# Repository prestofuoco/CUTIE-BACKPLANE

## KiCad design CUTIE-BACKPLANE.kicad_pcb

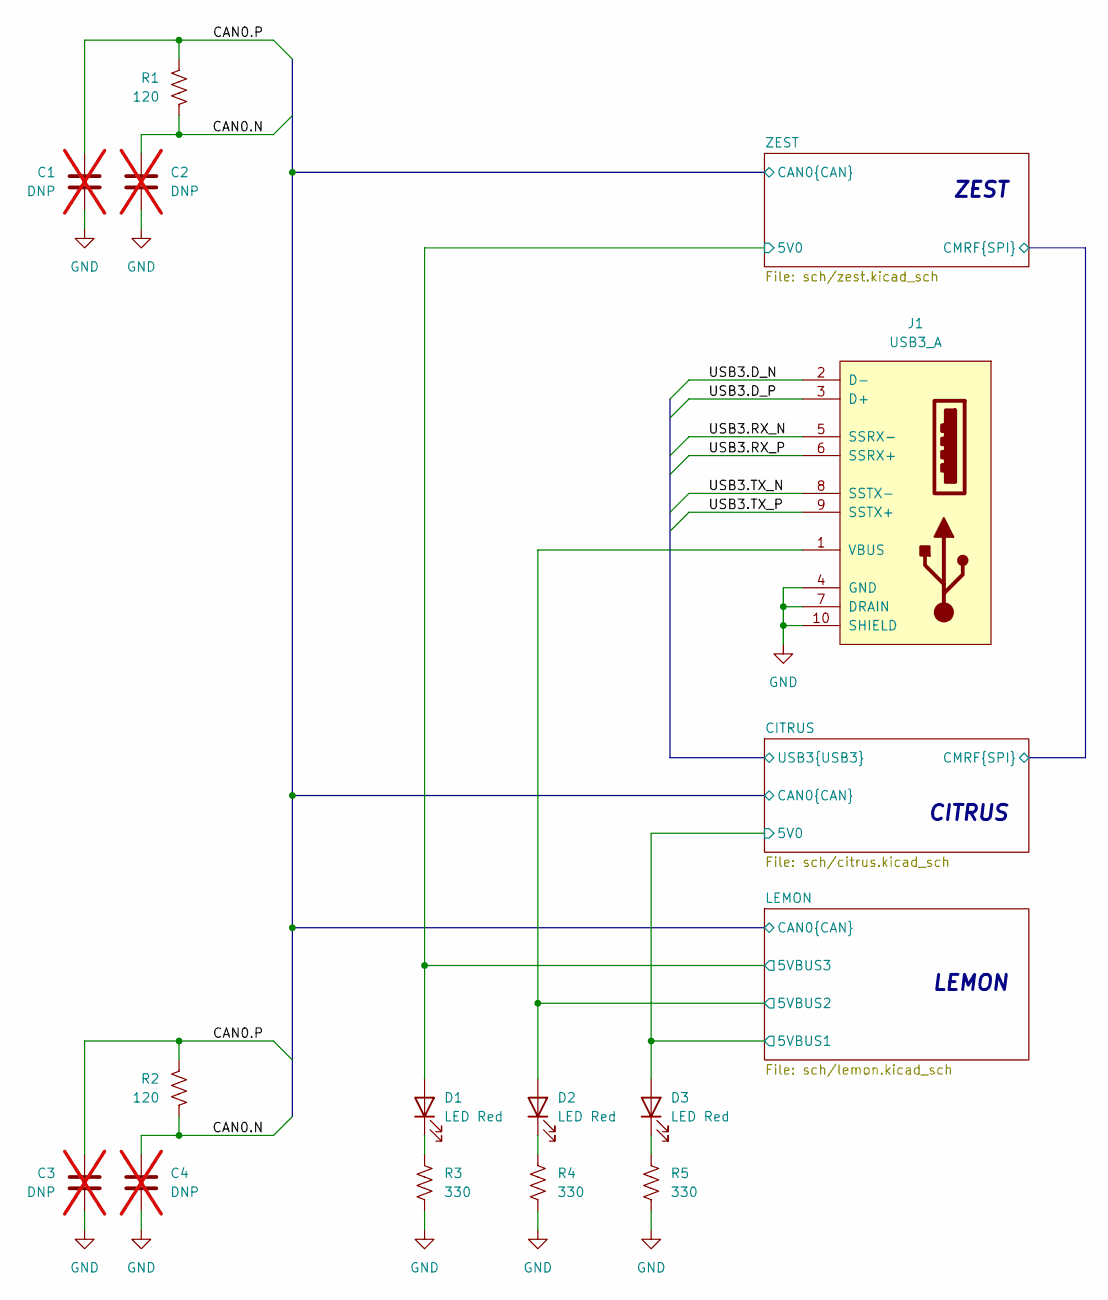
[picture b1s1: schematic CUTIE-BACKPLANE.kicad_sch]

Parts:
C1, C2, C3, C4: DNP; C_0402_1005Metric; not fitted
D1, D2, D3: LED Red; LED_0805_2012Metric
J1: USB3_A; CONN9_08-0003_MOL
R1, R2: 120; R_0402_1005Metric
R3, R4, R5: 330; R_0402_1005Metric

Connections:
/CITRUS/5V0: D3.2 (A); also elsewhere on the board
/CITRUS/CAN0.N: C2.2, C4.2, R1.2, R2.2; also elsewhere on the board
/CITRUS/CAN0.P: C1.2, C3.2, R1.1, R2.1; also elsewhere on the board
/CITRUS/USB3.D_N: J1.2 (D-); also elsewhere on the board
/CITRUS/USB3.D_P: J1.3 (D+); also elsewhere on the board
/CITRUS/USB3.RX_N: J1.5 (SSRX-); also elsewhere on the board
/CITRUS/USB3.RX_P: J1.6 (SSRX+); also elsewhere on the board
/CITRUS/USB3.TX_N: J1.8 (SSTX-); also elsewhere on the board
/CITRUS/USB3.TX_P: J1.9 (SSTX+); also elsewhere on the board
/LEMON/5VBUS2: D2.2 (A), J1.1 (VBUS); also elsewhere on the board
/LEMON/5VBUS3: D1.2 (A); also elsewhere on the board
GND: C1.1, C2.1, C3.1, C4.1, J1.4 (GND), J1.7 (DRAIN), J1.10 (SHIELD), R3.2, R4.2, R5.2; also elsewhere on the board
unnamed: D1.1 (K), R3.1
unnamed: D2.1 (K), R4.1
unnamed: D3.1 (K), R5.1

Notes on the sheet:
CITRUS
ZEST
LEMON

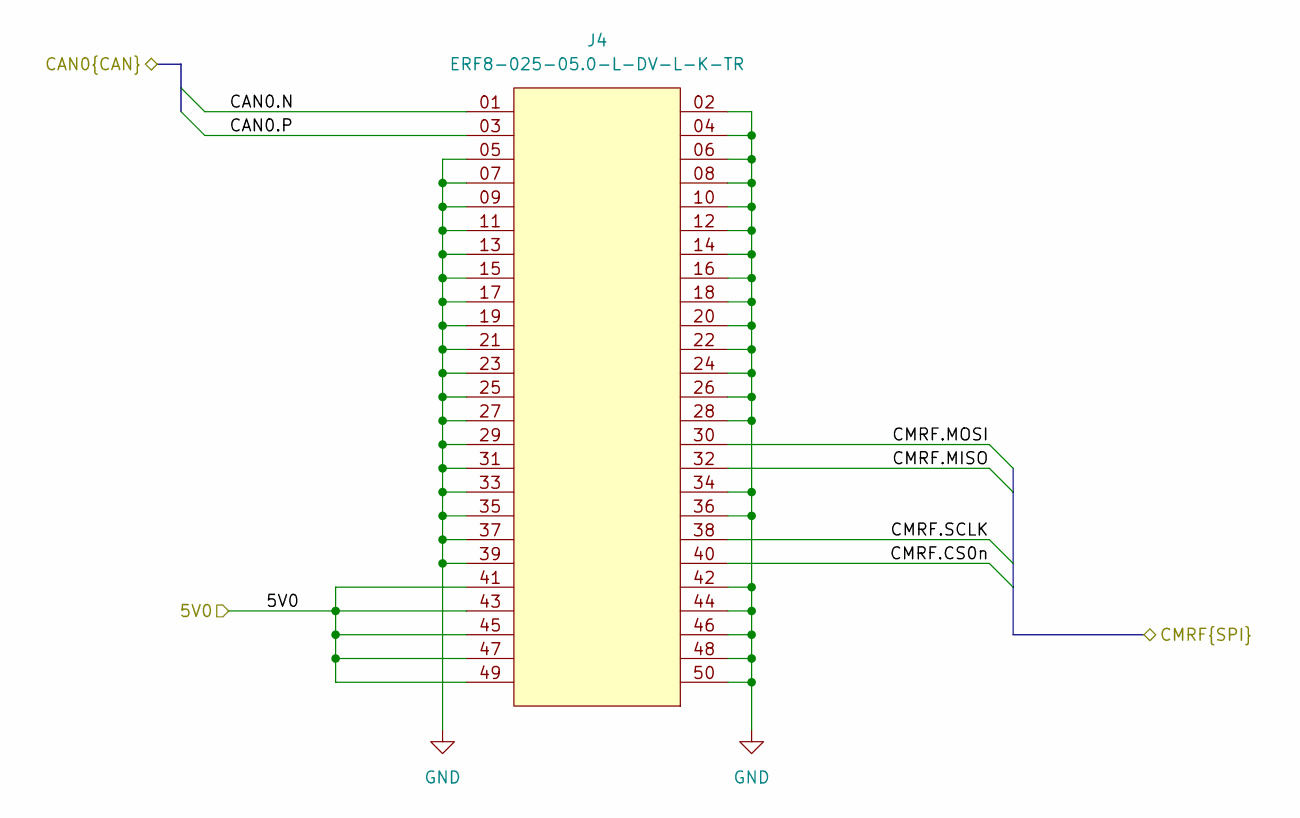
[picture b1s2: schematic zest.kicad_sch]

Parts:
J4: ERF8-025-05.0-L-DV-L-K-TR; SAMTEC_ERF8-025-05.0-L-DV-L-K-TR

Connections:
/CITRUS/CAN0.N: J4.01; also elsewhere on the board
/CITRUS/CAN0.P: J4.03; also elsewhere on the board
/CITRUS/CMRF.CS0n: J4.40; also elsewhere on the board
/CITRUS/CMRF.MISO: J4.32; also elsewhere on the board
/CITRUS/CMRF.MOSI: J4.30; also elsewhere on the board
/CITRUS/CMRF.SCLK: J4.38; also elsewhere on the board
/LEMON/5VBUS3: J4.41, J4.43, J4.45, J4.47, J4.49; also elsewhere on the board
GND: J4.02, J4.04, J4.05, J4.06, J4.07, J4.08, J4.09, J4.10, J4.11, J4.12, J4.13, J4.14, J4.15, J4.16, J4.17, J4.18, J4.19, J4.20, J4.21, J4.22, J4.23, J4.24, J4.25, J4.26, J4.27, J4.28, J4.29, J4.31, J4.33, J4.34, J4.35, J4.36, J4.37, J4.39, J4.42, J4.44, J4.46, J4.48, J4.50; also elsewhere on the board

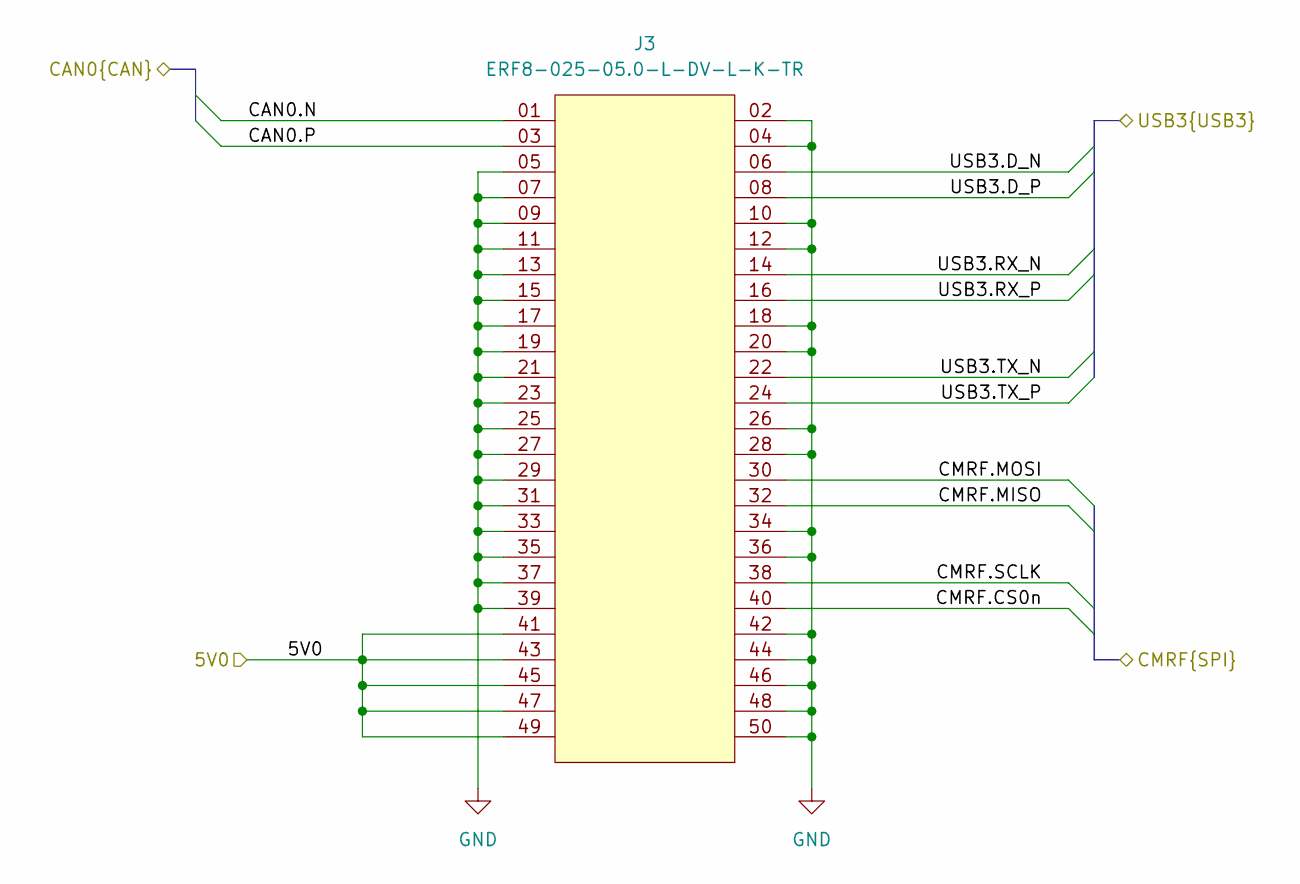
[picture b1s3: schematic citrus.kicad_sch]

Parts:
J3: ERF8-025-05.0-L-DV-L-K-TR; SAMTEC_ERF8-025-05.0-L-DV-L-K-TR

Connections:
/CITRUS/5V0: J3.41, J3.43, J3.45, J3.47, J3.49; also elsewhere on the board
/CITRUS/CAN0.N: J3.01; also elsewhere on the board
/CITRUS/CAN0.P: J3.03; also elsewhere on the board
/CITRUS/CMRF.CS0n: J3.40; also elsewhere on the board
/CITRUS/CMRF.MISO: J3.32; also elsewhere on the board
/CITRUS/CMRF.MOSI: J3.30; also elsewhere on the board
/CITRUS/CMRF.SCLK: J3.38; also elsewhere on the board
/CITRUS/USB3.D_N: J3.06; also elsewhere on the board
/CITRUS/USB3.D_P: J3.08; also elsewhere on the board
/CITRUS/USB3.RX_N: J3.14; also elsewhere on the board
/CITRUS/USB3.RX_P: J3.16; also elsewhere on the board
/CITRUS/USB3.TX_N: J3.22; also elsewhere on the board
/CITRUS/USB3.TX_P: J3.24; also elsewhere on the board
GND: J3.02, J3.04, J3.05, J3.07, J3.09, J3.10, J3.11, J3.12, J3.13, J3.15, J3.17, J3.18, J3.19, J3.20, J3.21, J3.23, J3.25, J3.26, J3.27, J3.28, J3.29, J3.31, J3.33, J3.34, J3.35, J3.36, J3.37, J3.39, J3.42, J3.44, J3.46, J3.48, J3.50; also elsewhere on the board

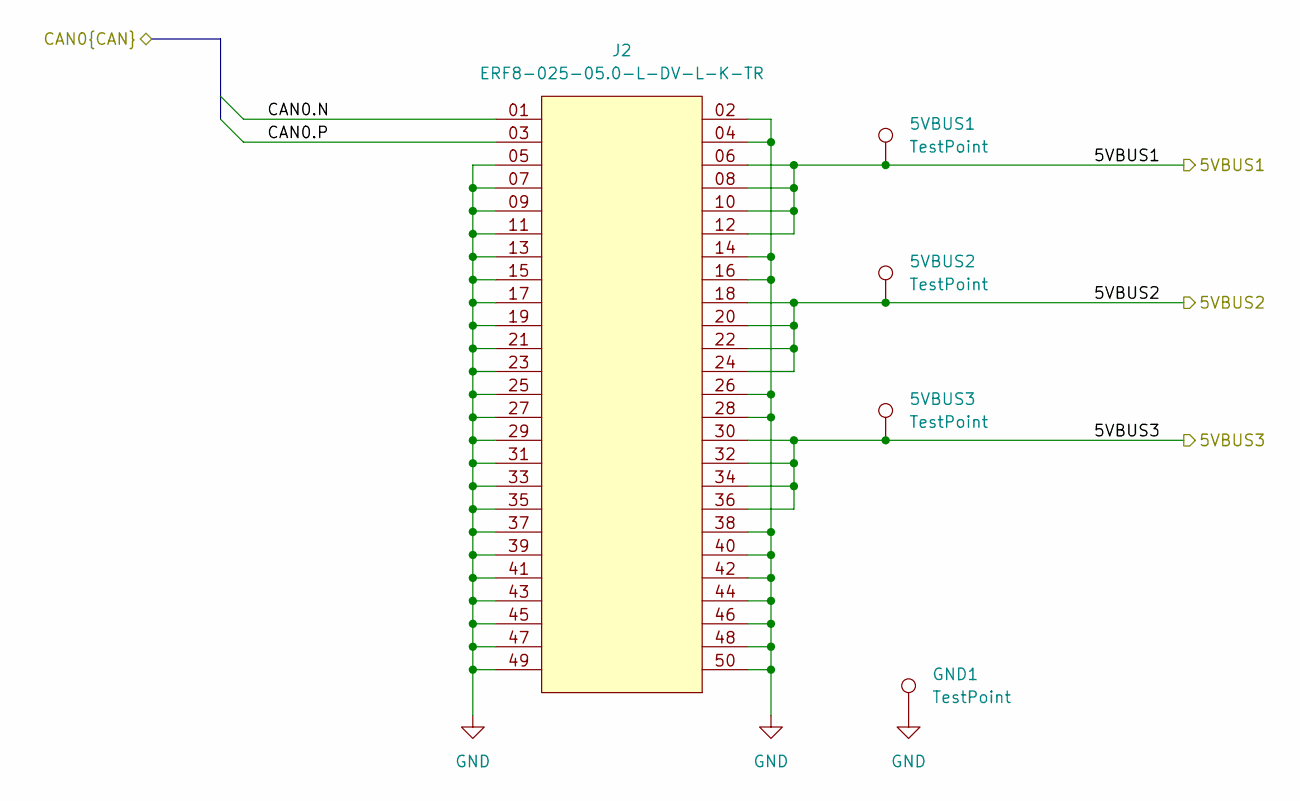
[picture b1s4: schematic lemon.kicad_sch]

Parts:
5VBUS1, 5VBUS2, 5VBUS3: TestPoint; KEYSTONE_575-4
GND1: TestPoint; KEYSTONE_575-4
J2: ERF8-025-05.0-L-DV-L-K-TR; SAMTEC_ERF8-025-05.0-L-DV-L-K-TR

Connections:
/CITRUS/5V0: 5VBUS1.1 (1_1), J2.06, J2.08, J2.10, J2.12; also elsewhere on the board
/CITRUS/CAN0.N: J2.01; also elsewhere on the board
/CITRUS/CAN0.P: J2.03; also elsewhere on the board
/LEMON/5VBUS2: 5VBUS2.1 (1_1), J2.18, J2.20, J2.22, J2.24; also elsewhere on the board
/LEMON/5VBUS3: 5VBUS3.1 (1_1), J2.30, J2.32, J2.34, J2.36; also elsewhere on the board
GND: GND1.1, J2.02, J2.04, J2.05, J2.07, J2.09, J2.11, J2.13, J2.14, J2.15, J2.16, J2.17, J2.19, J2.21, J2.23, J2.25, J2.26, J2.27, J2.28, J2.29, J2.31, J2.33, J2.35, J2.37, J2.38, J2.39, J2.40, J2.41, J2.42, J2.43, J2.44, J2.45, J2.46, J2.47, J2.48, J2.49, J2.50; also elsewhere on the board

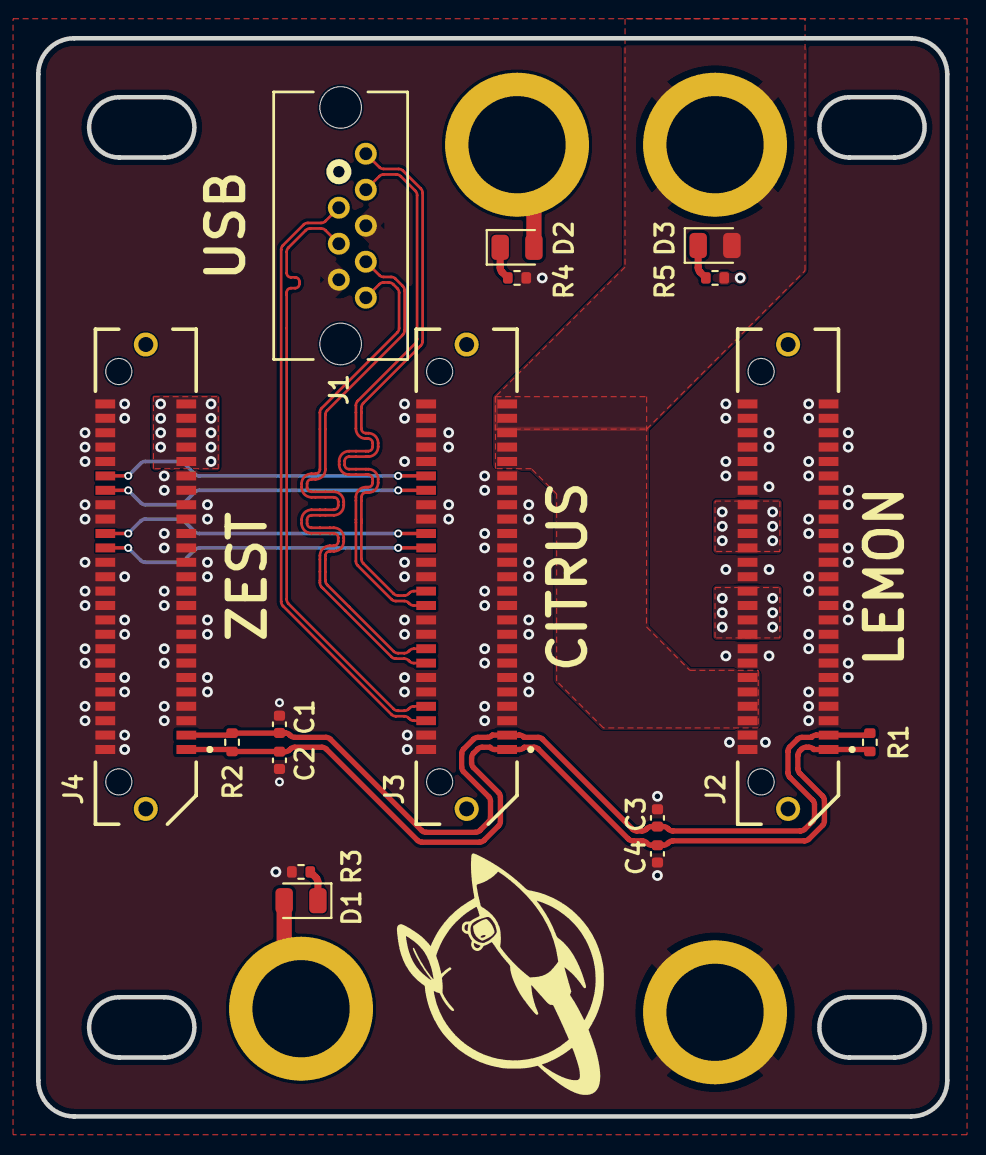
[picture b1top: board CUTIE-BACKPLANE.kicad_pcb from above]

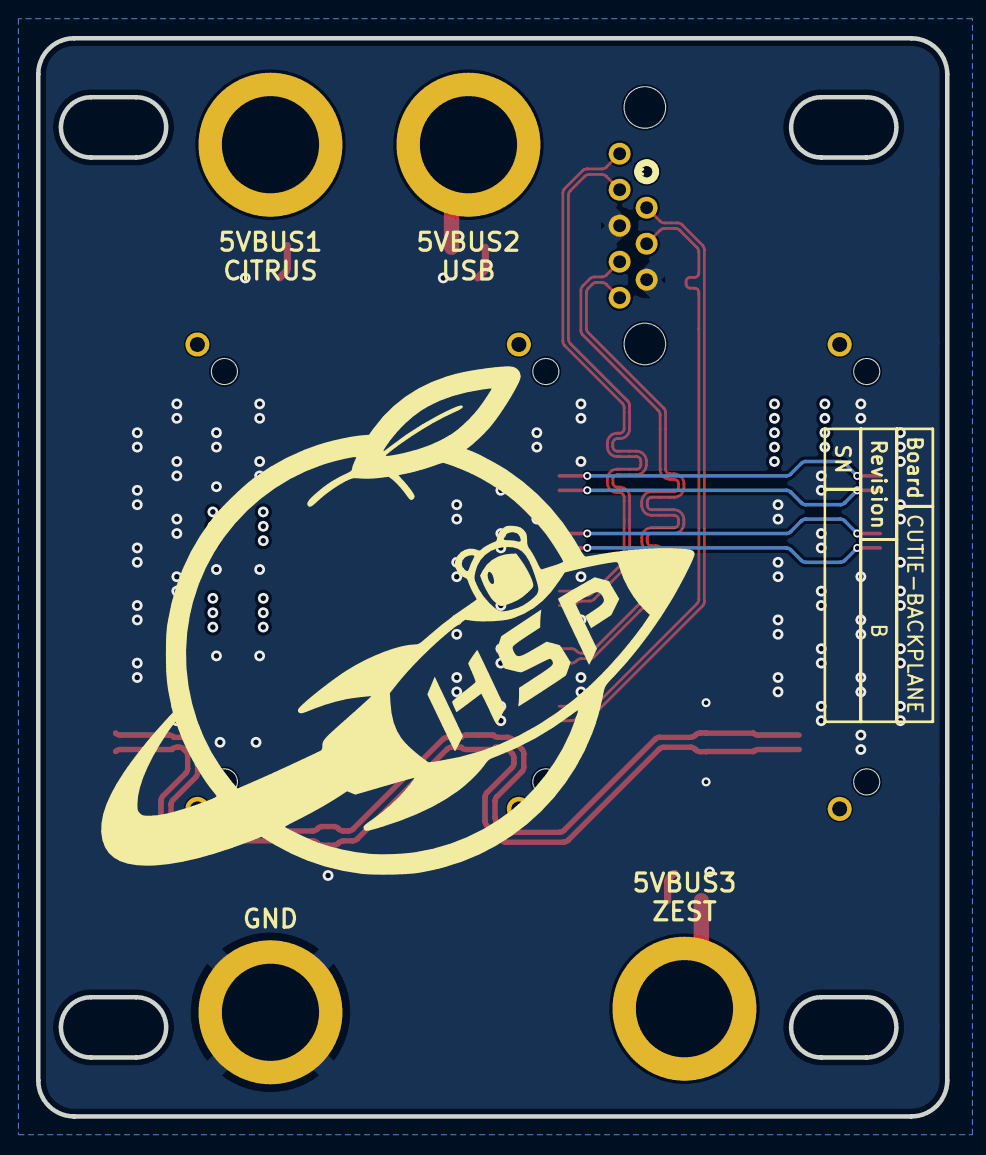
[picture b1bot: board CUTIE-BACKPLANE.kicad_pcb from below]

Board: 4 copper layers, 50.5 x 59.9 mm, 20 parts (4 on the bottom side), 19 nets.

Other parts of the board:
GND: TestPoint; KEYSTONE_575-4

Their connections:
GND: GND.1 (1_1); also elsewhere on the board

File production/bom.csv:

Designator,Footprint,Quantity,Value,LCSC Part #
"5VBUS1, 5VBUS2, 5VBUS3, GND",KEYSTONE_575-4,4,TestPoint,
"D1, D2, D3",0805,3,LED Red,
J1,CONN9_08-0003_MOL,1,USB3_A,
"J2, J3, J4",SAMTEC_ERF8-025-05.0-L-DV-L-K-TR,3,ERF8-025-05.0-L-DV-L-K-TR,
"R1, R2",0402,2,120,
"R3, R4, R5",0402,3,330,

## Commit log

2025-12-16 final setup for power rails
2025-12-23 initialized for 4-card
2025-12-23 fixed footprint link
2025-12-30 added pwr leds and edge cuts
2025-12-30 prelim layout complete
2025-12-30 added stephen's dxfs
2026-01-05 silkscreen edits
2026-01-06 added pdf
2026-01-12 added dnps for can filtering
2026-04-02 added tps and new init layout
2026-04-03 layout complete pending review
2026-04-03 added fabrication outputs
2026-04-03 moved connectors, added silkscreen
2026-04-08 push for fab
2026-04-21 rev b, flipped connectors
2026-04-21 mechanical spacing
2026-04-21 added thermal reliefs for pth
2026-04-22 rotated 3d models
2026-04-22 fillet traces
2026-04-22 edited silkscreens for fab
